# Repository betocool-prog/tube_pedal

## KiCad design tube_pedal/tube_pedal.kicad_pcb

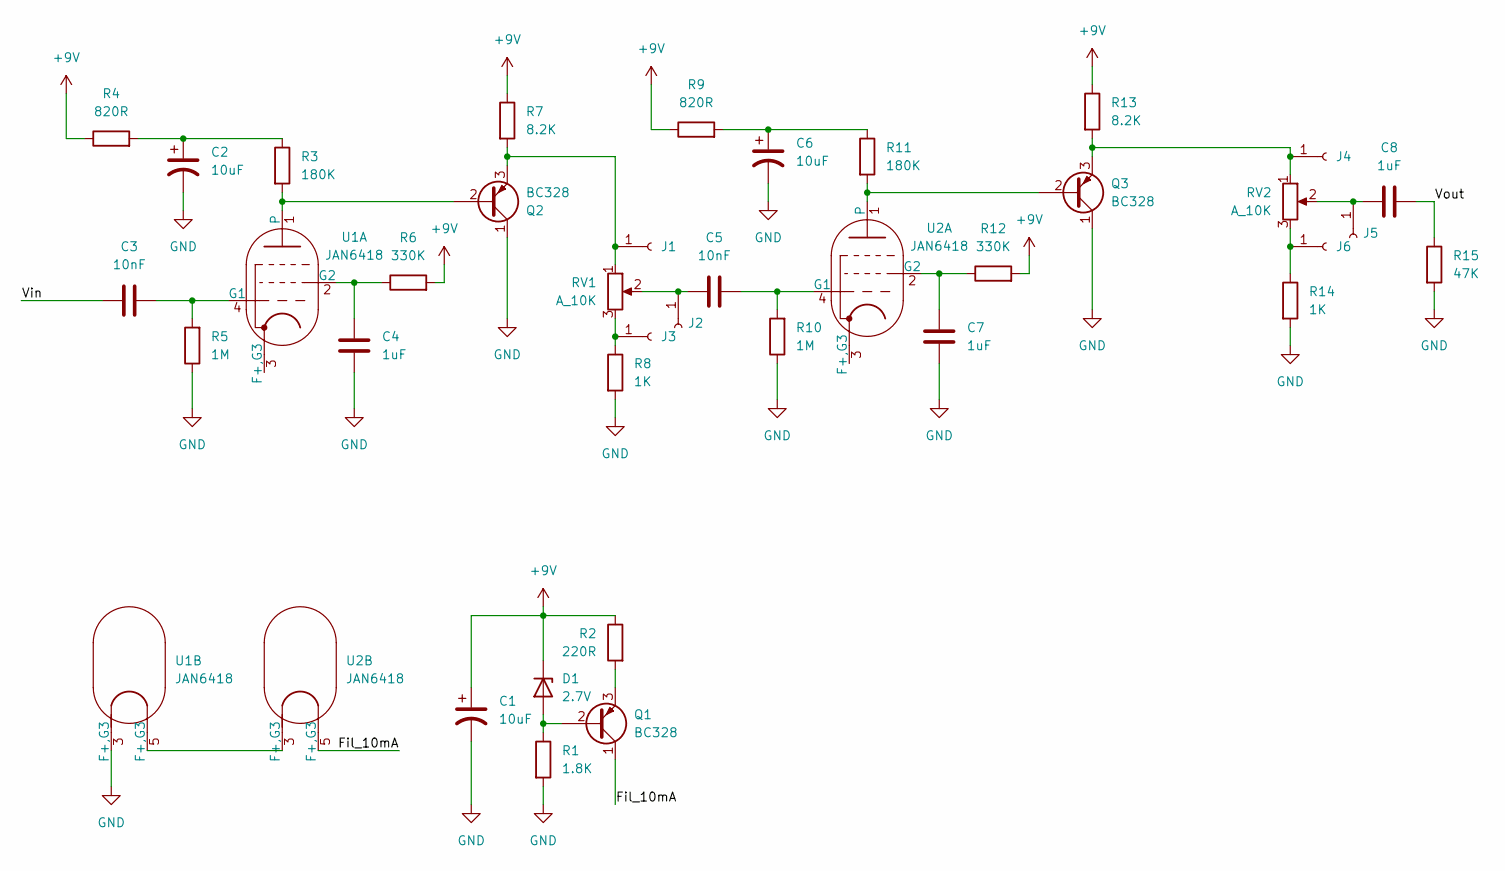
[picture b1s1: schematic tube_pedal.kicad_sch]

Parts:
C1, C2, C6: 10uF; CP_Radial_D5.0mm_P2.50mm
C3, C5: 10nF; C_Rect_L7.0mm_W4.5mm_P5.00mm
C4, C7, C8: 1uF; C_Rect_L7.0mm_W4.5mm_P5.00mm
D1: 2.7V; D_T-1_P10.16mm_Horizontal
J1, J2, J3, J4, J5, J6: Conn_01x01_Socket; SolderWire-0.1sqmm_1x01_D0.4mm_OD1mm
Q1, Q2, Q3: BC328; TO-92_Inline
R1: 1.8K; R_Axial_DIN0207_L6.3mm_D2.5mm_P10.16mm_Horizontal
R2: 220R; R_Axial_DIN0207_L6.3mm_D2.5mm_P10.16mm_Horizontal
R3, R11: 180K; R_Axial_DIN0207_L6.3mm_D2.5mm_P10.16mm_Horizontal
R4, R9: 820R; R_Axial_DIN0207_L6.3mm_D2.5mm_P10.16mm_Horizontal
R5, R10: 1M; R_Axial_DIN0207_L6.3mm_D2.5mm_P10.16mm_Horizontal
R6, R12: 330K; R_Axial_DIN0207_L6.3mm_D2.5mm_P10.16mm_Horizontal
R7, R13: 8.2K; R_Axial_DIN0207_L6.3mm_D2.5mm_P10.16mm_Horizontal
R8, R14: 1K; R_Axial_DIN0207_L6.3mm_D2.5mm_P10.16mm_Horizontal
R15: 47K; R_Axial_DIN0207_L6.3mm_D2.5mm_P10.16mm_Horizontal
RV1, RV2: A_10K; Potentiometer_Piher_T-16H_Single_Horizontal
U1, U2: JAN6418; Valve_Mini_Pentode_Linear

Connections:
+9V: C1.1, D1.1 (K), R2.1, R4.1, R6.2, R7.1, R9.1, R12.2, R13.1
/Fil_10mA: Q1.1 (C), U2.5 (F+,G3)
/Vin: C3.1
/Vout: C8.1, R15.1
GND: C1.2, C2.2, C4.1, C6.2, C7.1, Q2.1 (C), Q3.1 (C), R1.2, R5.1, R8.2, R10.1, R14.2, R15.2, U1.3 (F+,G3)
unnamed: C2.1, R3.1, R4.2
unnamed: C6.1, R9.2, R11.1
unnamed: D1.2 (A), Q1.2 (B), R1.1
unnamed: J1.1, Q2.3 (E), R7.2, RV1.1
unnamed: C5.1, J2.1, RV1.2
unnamed: J3.1, R8.1, RV1.3
unnamed: J4.1, Q3.3 (E), R13.2, RV2.1
unnamed: C8.2, J5.1, RV2.2
unnamed: J6.1, R14.1, RV2.3
unnamed: Q1.3 (E), R2.2
unnamed: Q2.2 (B), R3.2, U1.1
unnamed: Q3.2 (B), R11.2, U2.1
unnamed: C3.2, R5.2, U1.4 (G1)
unnamed: C4.2, R6.1, U1.2 (G2)
unnamed: U1.5 (F+,G3), U2.3 (F+,G3)
unnamed: C5.2, R10.2, U2.4 (G1)
unnamed: C7.2, R12.1, U2.2 (G2)

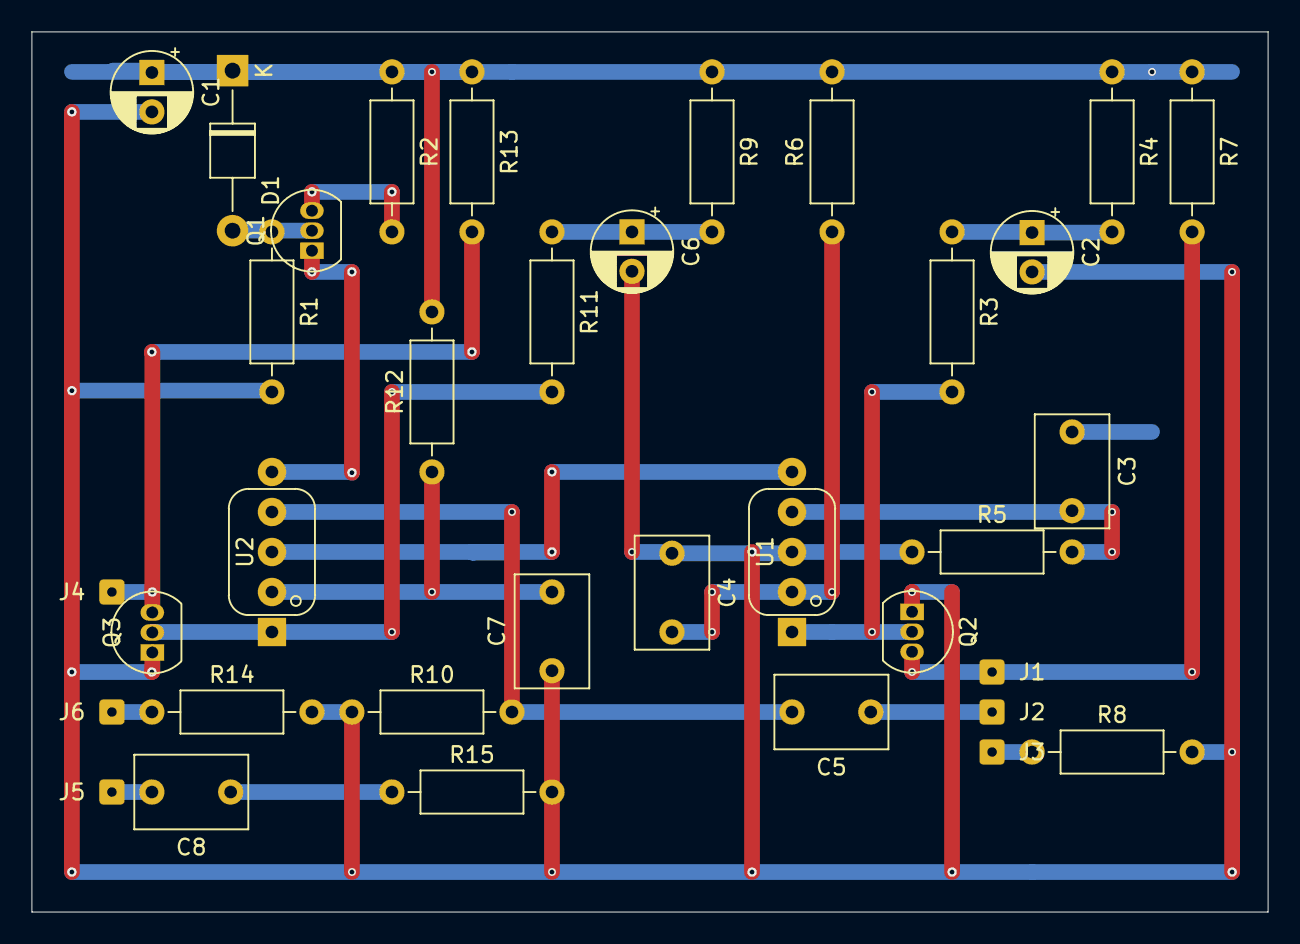
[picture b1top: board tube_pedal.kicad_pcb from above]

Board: 2 copper layers, 78.5 x 55.9 mm, 35 parts (0 on the bottom side), 21 nets.

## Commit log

2024-12-31 Empty commit
2025-01-02 First version on veroboard.
2025-01-02 Changed voltage cap.
2025-01-02 Updated grid origin.
2025-01-02 Minor changes.
